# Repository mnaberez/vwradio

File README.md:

# VW Radios

This repository is all about reverse engineering older Volkswagen car radios, like the Premium 5 radio shown above.  The radios studied here are over fifteen years old and are the single-DIN size.  Despite their age, they are intelligent and support on-board diagnostics (using VW's KWP1281 protocol on the K-line).  You'll find notes about protocols and hardware here, along with partial disassembles of firmware, but no original binaries of firmware or EEPROMs.

VW radios from this era require a four digit security code often referred to as the "SAFE code". The radios usually store the SAFE code in a serial EEPROM like a 93C46 or a 24C04. The SAFE code can be found by opening up the radio, desoldering the EEPROM, reading it, and then soldering the EEPROM back in. I wanted to know if there was an easier way.

I disassembled the firmware for these radios: Premium 4 (Clarion), Premium 5 (Delco), Gamma 5 (TechniSat), and Rhapsody (TechniSat).  I found that all of them have backdoors to read the SAFE code via on-board diagnostics.  Reading the code this way means the radio does not need to be opened and may not even need to be removed from the car.  Since this information is not published anywhere and I couldn't find any tool that could do it, I built my own tool.

## Projects

- [`kwp1281_tool`](./kwp1281_tool/):  Diagnostics protocol tool (Volkswagen [KWP1281](https://translate.google.com/translate?hl=en&sl=de&tl=en&u=https%3A%2F%2Fde.wikipedia.org%2Fwiki%2FKWP1281)).  It can send arbitrary commands to a radio, or any other module, using the KWP1281 protocol.  It can also send commands using a proprietary protocol found in TechniSat radios.  Finally, it can automatically retrieve the SAFE code for any of the radios listed above.

- [`faceplate_emulator`](./faceplate_emulator/): Faceplate emulator (NEC [µPD16432B](http://6502.org/documents/datasheets/nec/nec_upd16432b_2000_dec.pdf)).  It plugs into the Premium 4 radio in place of the faceplate and allows the radio to be controlled over serial.  It can also simultaneously control a real faceplate.

- [`tape_emulator`](./tape_emulator/): Cassette tape emulator (Philips TDA3612).  It plugs into the Premium 4 radio in place of the SCA4.4/TDA3612 cassette tape assembly and fools the radio into thinking a tape is playing.

- [`volume_monitor`](./volume_monitor/): Volume monitor (Mitsubishi [M62419FP](https://web.archive.org/web/20180328173343/http://pdf.datasheetcatalog.com/datasheet/MitsubishiElectricCorporation/mXrwwyx.pdf)).
It connects in parallel with the M62419FP sound controller used in the Premium 4 radio and sends updates over serial whenever the sound registers are changed.

- [`reverse_engineering`](./reverse_engineering/): Notes about the radios from reverse engineering, including commented disassembly listings of radio firmware.  This repository does not contain any original firmware or EEPROM binaries.

## Discoveries

Here are some of the more interesting discoveries I made about the radios:

- All of the radios studied support a common set of KWP1281 diagnostics functions on the normal radio address of 0x56.  Some radios (not all) also have protected KWP1281 commands on this same address.  The protected commands available vary by model but may include the ability to read the microcontroller's ROM or RAM, and to read/write serial EEPROM(s).  Accessing the protected commands requires sending a login block based on the SAFE code and also performing a group reading of a hidden group.

- VW Premium 4 (Clarion) has an unprotected KWP1281 command 0xF0 that returns the SAFE code.  It also contains a hidden mode where the SAFE code can be changed via the faceplate.  Entering this mode requires pressing keys that do not exist on the faceplate.  I assume there was a special manufacturing faceplate used by the factory.

- VW Premium 5 (Delco) and Seat Liceo (Delco) respond to a different set of KWP1281 commands on address 0x7C.  These commands require authentication using a hardcoded login block.  Once authenticated, commands are available to read and write the EEPROM, which can be used to retrieve the SAFE code.

- VW Gamma 5 (TechniSat) and Rhapsody (TechniSat) have a proprietary, non-KWP protocol on address 0x7C.  It is unlike anything that I have found documented and was likely made by TechniSat just for manufacturing of the radio.  It has commands to read and write the EEPROM, which can be used to retrieve the SAFE code.  The SAFE code area of the EEPROM is normally filtered from these commands, but another command disables the filtering.

## Spin-offs

I also developed several other projects as a side effect of this work:

- [premium5](https://github.com/mnaberez/premium5): VW Premium 5 car radio emulator and debugger with a web-based interface

- [k0emu](https://github.com/mnaberez/k0emu): NEC 78K0 instruction set emulator with cycle counting and peripheral device support

- [k0dasm](https://github.com/mnaberez/k0dasm): NEC 78K0 disassembler that generates output compatible with the [as78k0](http://shop-pdp.net/ashtml/as78k0.htm) assember

- [f2mc8dump](https://github.com/mnaberez/f2mc8dump): Exploit to dump the internal ROM of Fujitsu F2MC-8L microcontrollers with external bus

- [f2mc8dasm](https://github.com/mnaberez/f2mc8dasm): Fujitsu F2MC-8 disassembler that generates output compatible with the [asf2mc8](http://shop-pdp.net/ashtml/asf2mc.htm) assembler

- [m740dasm](https://github.com/mnaberez/m740dasm): Mitsubishi 740 disassembler that generates output compatible with the [as740](http://shop-pdp.net/ashtml/as740.htm) assembler

## Author

[Mike Naberezny](https://github.com/mnaberez)

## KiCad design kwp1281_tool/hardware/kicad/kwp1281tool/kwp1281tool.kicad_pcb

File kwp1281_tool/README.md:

# KWP1281 Tool

## Overview

This is a USB interface that connects to the K-line of a vehicle's OBD port or to the K-line of a control module on a bench.  It uses a microcontroller that has been programmed to implement the [KWP1281](https://de.wikipedia.org/wiki/KWP1281) protocol.

When I reverse engineered the firmware for the VW Premium 4 radio, I found that it responds to several hidden KWP1281 commands.  I wanted to send these commands but I had no way to do so.  The commercial scan tool that I was using at the time did not provide any access to the underlying communications.  I built this project so I could directly interact with the Premium 4 radio using the raw KWP1281 protocol.  I have since used it successfully on other modules as well.

There are other open source projects that implement KWP1281 but this project is not based on any of them.  Therefore, it may have different features or problems than those other implementations.  VW did not release any documentation on KWP1281 to the public and I do not have any non-public information.  My implementation is based on my own [reverse engineering](../reverse_engineering/) of the diagnostics routines in several car radios, along with unofficial information posted by others online.

## Features

 - Galvanic isolation between the USB port and the OBD port
 - Automatically detects the baud rate of the module
 - Capable of sending and receiving raw KWP1281 blocks
 - Outputs a transcript of all KWP1281 blocks sent and received
 - Checks for errors whenever possible, during both transmit and receive
 - Reliably maintains a connection for long periods with modules tested

## Design

This project uses its own hardware based on a microcontroller.  It is not compatible with a "dumb" cable, "KKL" cable, or any commercial cable.  Please do not ask me to add support for any other cables.

When I started out on this project, I tried several "dumb" interfaces but found that communication was often unreliable due to timing problems, especially when transferring a lot of data or trying to communicate over long periods of time.  Here are some issues with "dumb" cables:

 - A module must be woken up with "slow init" by sending its address at a nonstandard baud rate (5 baud).  Since the computer must bit-bang the address byte when using a "dumb" cable, timing can be an issue.  The module may fail to recognize its address if any unexpected delays occur on the computer during bit-banging.

 - The protocol is designed for automatic baud rate detection.  After a module wakes up, it sends a sync byte (0x55) so that the receiver can measure its baud rate.  To detect the baud rate reliably, a timer with microsecond precision is needed.  This can't be done with a "dumb" cable so either the user has to pre-select a baud rate or various baud rates have to be blindly tried until one works.

 - Modules are sensitive to timing between bytes.  Once a connection is established, modules typically require a delay of one millisecond before each byte in a block is transmitted.  However, if the byte is delayed by too many milliseconds, the module may return "no acknowledge" or may abort the connection entirely.  Delays between the bytes caused by the computer's operating system multitasking or the USB to serial adapter can cause the KWP1281 connection to be unreliable when using a "dumb" cable.

This project uses a microcontroller to solve the above issues, which is how most commercial interfaces are implemented as well.  Again, please do not ask me to support other cables.

## Usage

Build the hardware as described in [`hardware/`](./hardware/).  Modify the [`main.c`](./firmware/main.c) file in the firmware for the KWP1281 communications you want to perform.  Build and flash the firmware.  Connect the board to the module.  When the board is powered up, it will begin KWP1281 communications immediately.  Use any terminal program to view the debug output.

Example code for `main.c`:
```
kwp_result_t result = kwp_connect(KWP_RADIO);
kwp_panic_if_error(result);

result = kwp_read_group(1);
kwp_panic_if_error(result);
```

Corresponding debug output:
```
CONNECT 56
BAUD: 10400 (DETECTED 10482)
KWRECV: 01 8A
KWSEND: 75
RECV: 0F AD F6 31 4A 30 30 33 35 31 38 30 42 20 20 03
PERFORM ACK
SEND: 03 AE 09 03
RECV: 0F AF F6 20 52 61 64 69 6F 20 44 45 32 20 20 03
PERFORM ACK
SEND: 03 B0 09 03
RECV: 0E B1 F6 20 20 20 20 20 20 20 30 30 30 31 03
PERFORM ACK
SEND: 03 B2 09 03
RECV: 08 B3 F6 00 03 21 86 9F 03
PERFORM ACK
SEND: 03 B4 09 03
RECV: 03 B5 09 03
VAG Number: "1J0035180B  "
Component:  " Radio DE2         0001"
PERFORM GROUP READ
SEND: 04 B6 29 01 03
RECV: 0F B7 E7 25 00 00 06 5F 80 17 64 00 25 00 87 03
MEAS: GROUP=01 CELL=01 FORMULA=25 VALUE=0000
MEAS: GROUP=01 CELL=02 FORMULA=06 VALUE=5F80
MEAS: GROUP=01 CELL=03 FORMULA=17 VALUE=6400
MEAS: GROUP=01 CELL=04 FORMULA=25 VALUE=0087
```

The tool has been tested successfully with over twenty different modules (mostly car radios).  It has been extensively tested with the the VW Premium 5 radio (Delco) and the VW Golf/Jetta Mk3 ABA 2.0L Motronic M5.9 ECU (Bosch).  It can maintain a connection reliably with these modules for hours.

## Pass-through Mode

Pass-through mode allows the host PC to directly control the K-line so that software written for "dumb" cables can be used with this interface.  Although I do not generally recommend this due to the issues with "dumb" cables noted above, the pass-through mode can be used if you need to run a piece of software that only supports "dumb" cables.

Enable the pass-through mode:

```
passthru_enable();
while(1);
```

In pass-through mode, the TXD and RXD of the onboard FT232RL are connected directly to the K-line via the L9637D.  The microcontroller's UARTs will still be able to receive data from the host PC and the K-line but they can't transmit to either.

Pass-through mode is also activated if the microcontroller is not installed or is held in reset.

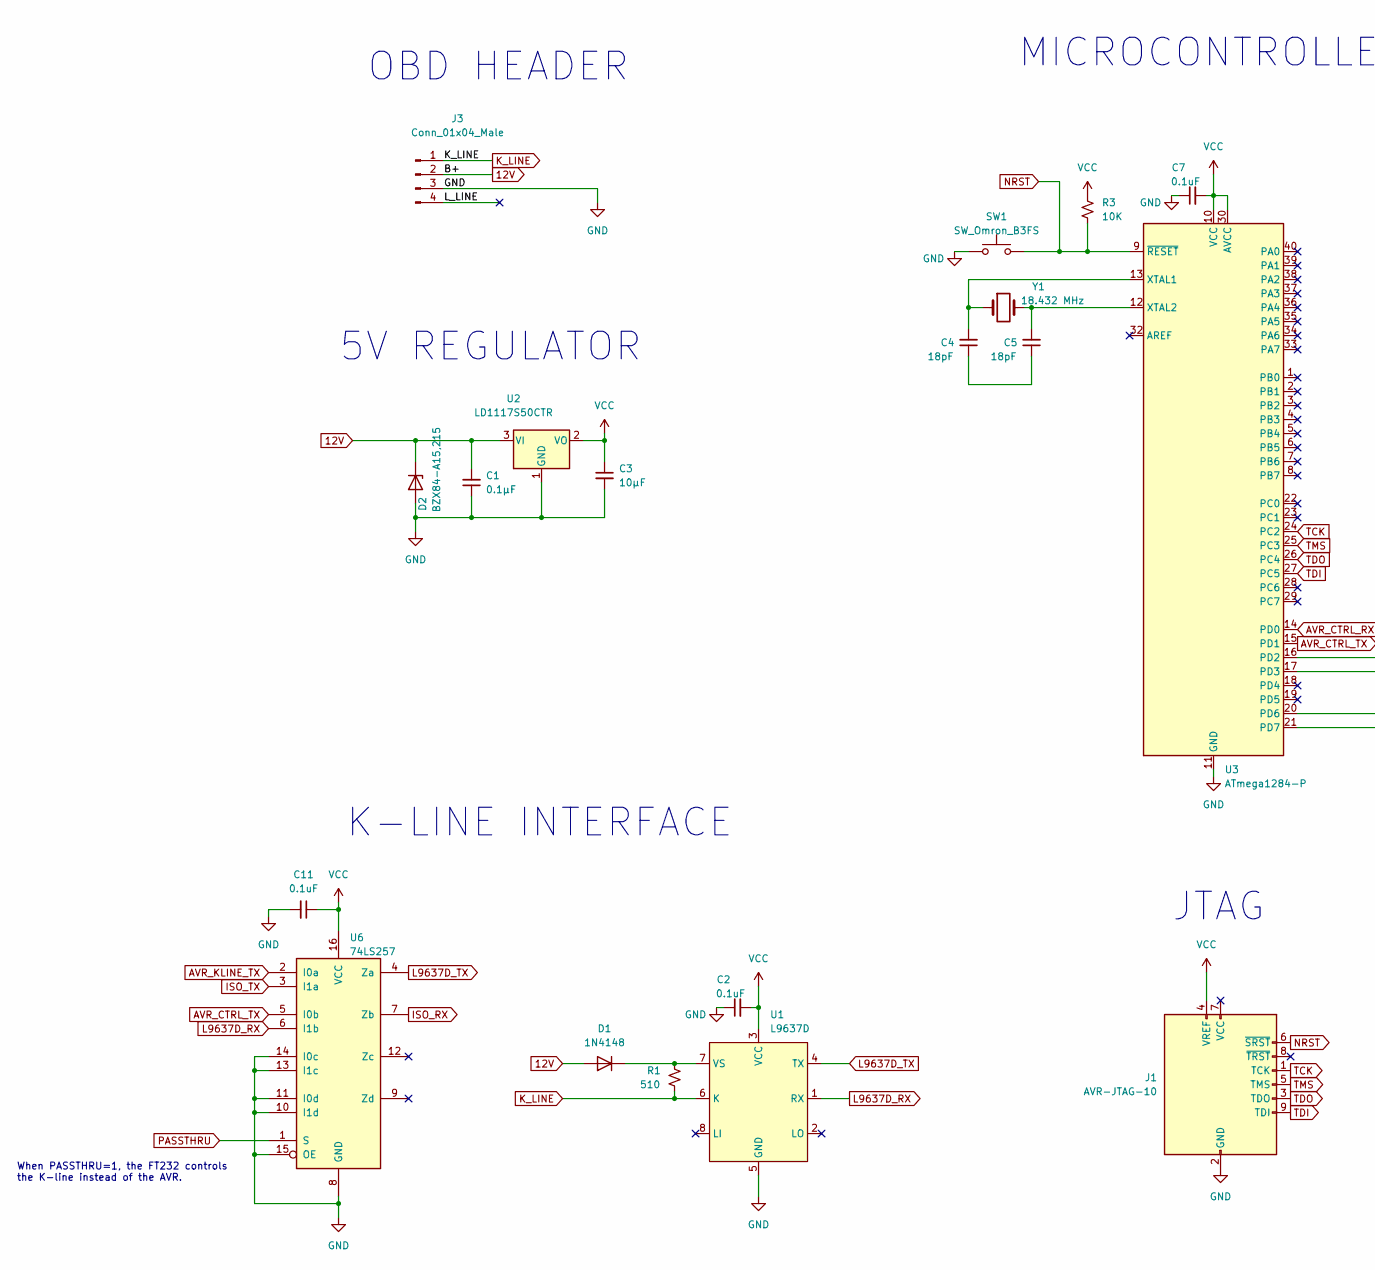
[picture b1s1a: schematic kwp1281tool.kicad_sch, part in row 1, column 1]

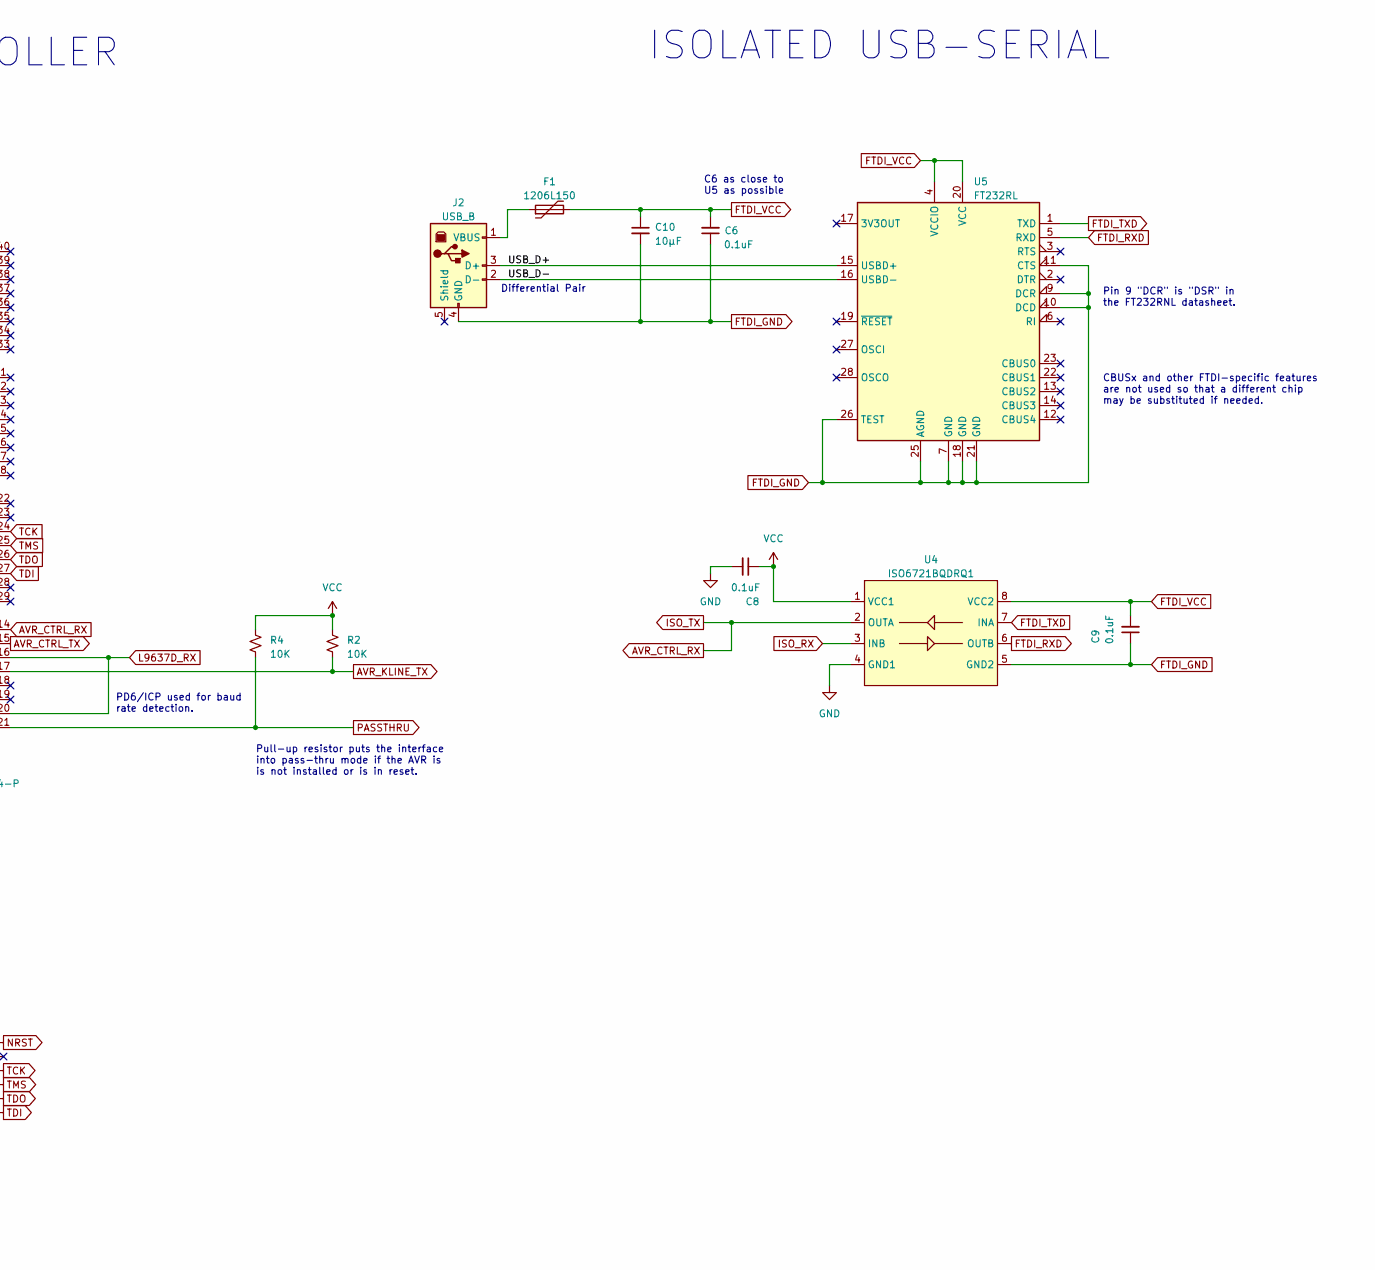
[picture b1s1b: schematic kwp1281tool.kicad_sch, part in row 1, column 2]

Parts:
C1: 0.1μF; C_0805_2012Metric_Pad1.18x1.45mm_HandSolder
C2, C6, C8, C9: 0.1uF; C_0805_2012Metric_Pad1.18x1.45mm_HandSolder
C3, C10: 10μF; C_0805_2012Metric_Pad1.18x1.45mm_HandSolder
C4, C5: 18pF; C_Disc_D5.0mm_W2.5mm_P5.00mm
C7, C11: 0.1uF; C_Disc_D5.0mm_W2.5mm_P5.00mm
D1: 1N4148; D_DO-35_SOD27_P7.62mm_Horizontal
D2: BZX84-A15,215; SOT-23
F1: 1206L150; Fuse_1206_3216Metric_Pad1.42x1.75mm_HandSolder
J1: AVR-JTAG-10; avr_jtag
J2: USB_B; USB_B_OST_USB-B1HSxx_Horizontal
J3: Conn_01x04_Male; PinHeader_1x04_P2.54mm_Horizontal
R1: 510; R_Axial_DIN0207_L6.3mm_D2.5mm_P15.24mm_Horizontal
R2, R3, R4: 10K; R_Axial_DIN0204_L3.6mm_D1.6mm_P7.62mm_Horizontal
SW1: SW_Omron_B3FS; SW_TH_Tactile_Omron_B3F-10xx
U1: L9637D; SOIC-8_3.9x4.9mm_P1.27mm
U2: LD1117S50CTR; SOT-223-3_TabPin2
U3: ATmega1284-P; DIP-40_W15.24mm
U4: ISO6721BQDRQ1; SOIC-8_3.9x4.9mm_P1.27mm
U5: FT232RL; SSOP-28_5.3x10.2mm_P0.65mm
U6: 74LS257; DIP-16_W7.62mm
Y1: 18.432 MHz; Crystal_HC49-4H_Vertical

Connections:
12V: C1.2, D1.2 (A), D2.3 (K), J3.2, U2.3 (VI)
/L_LINE: J3.4
/USB_D+: J2.3 (D+), U5.15 (USBD+)
/USB_D-: J2.2 (D-), U5.16 (USBD-)
AVR_CTRL_RX: U3.14 (PD0), U4.2 (OUTA), U6.3 (I1a)
AVR_CTRL_TX: U3.15 (PD1), U6.5 (I0b)
AVR_KLINE_TX: R2.2, U3.17 (PD3), U6.2 (I0a)
FTDI_GND: C6.1, C9.1, C10.2, J2.4 (GND), U4.5 (GND2), U5.7 (GND), U5.9 (DCR), U5.10 (DCD), U5.11 (CTS), U5.18 (GND), U5.21 (GND), U5.25 (AGND), U5.26 (TEST)
FTDI_RXD: U4.6 (OUTB), U5.5 (RXD)
FTDI_TXD: U4.7 (INA), U5.1 (TXD)
FTDI_VCC: C6.2, C9.2, C10.1, F1.2, U4.8 (VCC2), U5.4 (VCCIO), U5.20 (VCC)
GND: C1.1, C2.1, C3.2, C7.1, C8.2, C11.2, D2.1 (A), J1.2 (GND), J1.10 (GND), J3.3, SW1.1, U1.5 (GND), U2.1 (GND), U3.11 (GND), U3.31 (GND), U4.4 (GND1), U6.8 (GND), U6.10 (I1d), U6.11 (I0d), U6.13 (I1c), U6.14 (I0c), U6.15 (OE)
ISO_RX: U4.3 (INB), U6.7 (Zb)
K_LINE: J3.1, R1.2, U1.6 (K)
L9637D_RX: U1.1 (RX), U3.16 (PD2), U3.20 (PD6), U6.6 (I1b)
L9637D_TX: U1.4 (TX), U6.4 (Za)
NRST: J1.6 (~SRST), R3.2, SW1.2, U3.9 (~RESET)
unnamed: C4.1, C5.1
unnamed: D1.1 (K), R1.1, U1.7 (VS)
unnamed: F1.1, J2.1 (VBUS)
unnamed: C4.2, U3.13 (XTAL1), Y1.1
unnamed: C5.2, U3.12 (XTAL2), Y1.2
PASSTHRU: R4.2, U3.21 (PD7), U6.1 (S)
TCK: J1.1 (TCK), U3.24 (PC2)
TDI: J1.9 (TDI), U3.27 (PC5)
TDO: J1.3 (TDO), U3.26 (PC4)
TMS: J1.5 (TMS), U3.25 (PC3)
VCC: C2.2, C3.1, C7.2, C8.1, C11.1, J1.4 (VREF), R2.1, R3.1, R4.1, U1.3 (VCC), U2.2 (VO), U3.10 (VCC), U3.30 (AVCC), U4.1 (VCC1), U6.16 (VCC)

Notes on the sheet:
When PASSTHRU=1, the FT232 controls the K-line instead of the AVR.
PD6/ICP used for baud rate detection.
MICROCONTROLLER
K-LINE INTERFACE
CBUSx and other FTDI-specific features are not used so that a different chip may be substituted if needed.
5V REGULATOR
Pull-up resistor puts the interface into pass-thru mode if the AVR is is not installed or is in reset.
Pin 9 "DCR" is "DSR" in the FT232RNL datasheet.
C6 as close to U5 as possible
OBD HEADER
ISOLATED USB-SERIAL
Differential Pair
JTAG

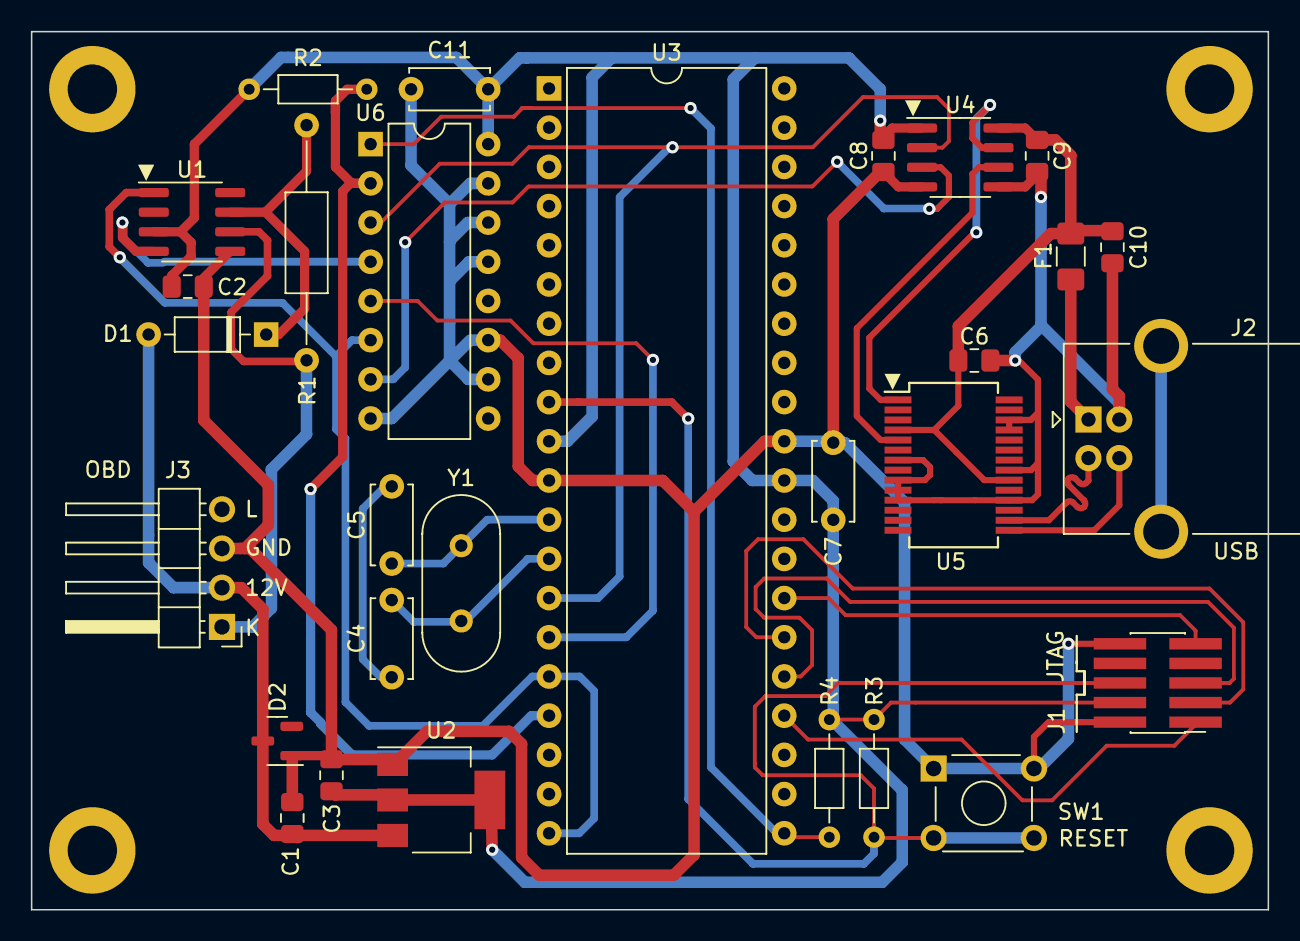
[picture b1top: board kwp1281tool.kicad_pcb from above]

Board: 2 copper layers, 80.1 x 56.9 mm, 29 parts (0 on the bottom side), 27 nets.

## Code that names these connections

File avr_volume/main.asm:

;VW Premium IV Radio (Clarion PU-1666A) Volume Monitor
;
;Passively captures SPI commands from the radio's microcontroller to its
;Mitsubishi M62419FP sound controller, decodes the commands, computes
;the programmed attenuator values in dB, then dumps the values out
;the UART at 115200 bps, N-8-1.
;
;Atmel ATMega1284 running at 20 MHz
;
;Pin  9: /RESET to GND through pushbutton, 10K pullup to Vcc
;               also connect to Atmel-ICE AVR port pin 6 nSRST
;Pin 10: Vcc (connect to radio's 5V)
;Pin 11: GND (connect to radio's GND)
;Pin 12: XTAL2 (to 20 MHz crystal with 18pF cap to GND)
;Pin 13: XTAL1 (to 20 MHz crystal and 18pF cap to GND)
;...
;Pin 15: PD1/TXD (to PC's serial RXD)
;...
;Pin 24: PC2 JTAG TCK (to Atmel-ICE AVR port pin 1 TCK)
;Pin 25: PC3 JTAG TMS (to Atmel-ICE AVR port pin 5 TMS)
;Pin 26: PC4 JTAG TDO (to Atmel-ICE AVR port pin 3 TDO)
;Pin 27: PC5 JTAG TDI (to Atmel-ICE AVR port pin 9 TDI)
;...
;Pin 30: AVCC connect directly to Vcc (also to Atmel-ICE AVR port pin 4 VTG)
;Pin 31: GND (also to Atmel-ICE AVR port pins 2 GND and 10 GND)
;Pin 32: AREF connect to GND through 0.1 uF cap
;...
;Pin 39: PA1 M62419FP Clock
;Pin 40: PA0 M62419FP Data
;

.include "m1284def.asm"


.equ ram             = SRAM_START
;Buffers for M62419FP command packets (isr buf -> rx buf -> work buf)
.equ packet_bitcount = ram      ;Counts down bits remaining to rx in packet
.equ packet_isr_buf  = ram+$01  ;2 bytes to accumulate SPI packet bits in ISR
.equ packet_rx_buf   = ram+$03  ;2 bytes for complete SPI packet received
.equ packet_work_buf = ram+$05 	;2 bytes for SPI packet used during parsing
;Buffer used to track M62419FP state across commands
.equ m62419fp_buf    = ram+$07  ;12 byte buffer for M62419FP state


;Offsets into M62419FP state buffer
.equ ch0             = 0                ;Channel 0 (Right):
.equ ch0_att1        = ch0+0            ;  ATT1 5-bit code
.equ ch0_att2        = ch0+1            ;  ATT2 2-bit code
.equ ch0_loudness    = ch0+2            ;  Loudness flag (0=off, 1=on)
.equ ch0_input       = ch0+3            ;  Input selector 2-bit code
.equ ch1             = ch0_input+1      ;Channel 1 (Left):
.equ ch1_att1        = ch1+0            ;  ATT1 5-bit code
.equ ch2_att2        = ch1+1            ;  ATT2 2-bit code
.equ ch3_loudness    = ch1+2            ;  Loudness bit (0=off, 1=on)
.equ ch4_input       = ch1+3            ;  Input selector 2-bit code
.equ common          = ch4_input+1      ;Common to both channels:
.equ fadesel         = common+0         ;  Fader Select flag (0=front, 1=rear)
.equ fader           = common+1         ;  Fader 4-bit code
.equ bass            = common+2         ;  Bass 4-bit tone code
.equ treble          = common+3         ;  Treble 4-bit tone code


.org 0
    rjmp reset

.org PCI0addr
	rjmp spi_isr_pcint0

.org 0+INT_VECTORS_SIZE


reset:
	ldi r16, low(RAMEND) 		;Initialize the stack pointer
	out SPL, r16
	ldi r16, high(RAMEND)
	out SPH, r16

	rcall uart_init 			;15200 bps, N-8-1
	rcall spi_init              ;Set up for M62419FP receive on interrupt
	sei                         ;Enable interrupts

loop:
    ;Set Y-pointer to a buffer that will receive a packet
    ldi YL, low(packet_work_buf)
    ldi YH, high(packet_work_buf)

    ;Set Z-pointer to M62419FP registers buffer
    ldi ZL, low(m62419fp_buf)
    ldi ZH, high(m62419fp_buf)

wait:
    ;Wait for an M62419FP command packet
    rcall spi_get_packet        ;Try to get a new packet into bufer at Y
    brcc wait                   ;Loop until one is ready

    rcall cmd_parse             ;Parse command at Y into registers at Z
    rcall cmd_parse             ;Parse command at Y into registers at Z
    rcall dump_to_uart
    rjmp loop


dump_to_uart:
;Dump the virtual M62419FP register state to the UART, along with
;the calculated attenuation values in dB.
;
;Format of the dump:
;  Byte  0: Number of bytes to follow
;  Byte  1: CH0 ATT1 5-bit code
;  Byte  2: CH0 ATT2 2-bit code
;  Byte  3: CH0 Attenuation (ATT1+ATT2) in signed dB
;  Byte  4: CH0 Loudness flag
;  Byte  5: CH0 Input Selector 2-bit code
;  Byte  6: CH1 ATT1 5-bit code
;  Byte  7: CH1 ATT2 2-bit code
;  Byte  8: CH1 Attenuation (ATT1+ATT2) in signed dB
;  Byte  9: CH1 Loudness flag
;  Byte 10: CH1 Input Selector 2-bit code
;  Byte 11: Fader Select flag
;  Byte 12: Fader 4-bit code
;  Byte 13: Fader Attenuation in signed dB
;  Byte 14: Bass 4-bit code
;  Byte 15: Bass tone in signed dB
;  Byte 16: Treble 4-bit code
;  Byte 17: Treble tone in signed dB
;
;Destroys R16, R17, R18, Z-pointer.
;
    ldi r16, 17
    rcall uart_send_byte        ;Send number of bytes to follow
    clr r18                     ;Channel number = 0
dump_loop:
    ;Set Z-pointer to buffer area for channel 0 or 1
    ldi ZL, low(m62419fp_buf)   ;Base address of M62419FP registers buffer
    ldi ZH, high(m62419fp_buf)
    sbrc r18, 0                 ;Skip next instruction if this is channel 0
    adiw ZH:ZL, ch1             ;Add offset for channel 1 registers

    ;Send ATT1 and ATT2 codes, calculate ATT1+ATT2 in dB and send it
    ld r16, Z+                  ;Load ATT1 code
    rcall uart_send_byte        ;Send it
    rcall cmd_calc_att1_db      ;Convert ATT1 to signed dB
    push r16                    ;Save ATT1 dB on the stack
    ld r16, Z+                  ;Load ATT2 code
    rcall uart_send_byte        ;Send it
    rcall cmd_calc_att2_db      ;Convert it to signed dB
    mov r17, r16                ;Move ATT2 dB into R17
    pop r16                     ;Recall ATT1 dB into R16
    rcall cmd_calc_att_sum_db   ;Caculate sum of R16 + R17 in signed dB
    rcall uart_send_byte        ;Send it

    ;Send other registers
    ld r16, Z+                  ;Load and send loudness
    rcall uart_send_byte
    ld r16, Z+                  ;Load and send input selector
    rcall uart_send_byte

    inc r18                     ;Increment channel number
    cpi r18, 2                  ;Finished both channels?
    brne dump_loop              ;  No: dump next channel

    ;Set Z-pointer to buffer area for fader
    ldi ZL, low(m62419fp_buf+common)
    ldi ZH, high(m62419fp_buf+common)

    ld r16, Z+                  ;Load and send fader select
    rcall uart_send_byte

    ld r16, Z+                  ;Load fader 4-bit code
    rcall uart_send_byte        ;Send it
    rcall cmd_calc_fader_db     ;Convert it to signed dB
    rcall uart_send_byte        ;Send it

    ld r16, Z+                  ;Load bass 4-bit code
    rcall uart_send_byte        ;Send it
    rcall cmd_calc_tone_db      ;Convert it to signed dB
    rcall uart_send_byte        ;Send it

    ld r16, Z+                  ;Load treble 4-bit code
    rcall uart_send_byte        ;Send it
    rcall cmd_calc_tone_db      ;Convert it to signed dB
    rcall uart_send_byte        ;Send it
    ret


.include "m62419fp_spi.asm"     ;M62419FP SPI receive
.include "m62419fp_cmd.asm"     ;M52419FP SPI command packet parsing
.include "uart.asm"             ;UART routines

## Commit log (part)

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2019-08-07 Found more sub_0c48 tables
2019-08-09 Found more code locations
2019-08-09 Remove hardcoded addresses
2019-08-09 Found block length in memory
2019-08-09 Comment unknown KWP1281 code
2019-08-10 Progress on KWP1281 initialization
2019-08-13 Add comments with text for states
2019-08-13 Fix pointers to group reading tables
2019-08-13 Add comments for I/O used in bit-banging address
2019-08-18 Progress on address 0x3f security access
2019-08-18 Found bit that controls SAFE mode lock/unlock
2019-08-22 Allow configuration of F_CPU via Makefile
2019-08-23 Add support for 8 and 16 MHz crystals
2019-08-23 Remove unused functions
2019-08-23 Fix "if" that should be "else if"
2019-09-06 Clarify error code description
2019-09-07 Add KWP1281 addresses to filenames
2019-09-08 Fix printing VAG number with "extra info" bit set
2019-09-09 Confirmed address 0x3f is the instrument cluster
2019-10-31 Use #pragma once
2019-10-31 Fix functions with no parameters
2019-10-31 Fix missing #pragma once
2019-11-02 Remove _autobaud_ prefix from statics
2019-11-09 Fix uninitialized variable warning
    kwp1281.c: In function ‘kwp_connect’:
    kwp1281.c:870:8: warning: ‘keyword’ may be used uninitialized in this function [-Wmaybe-uninitialized]
    if (keyword != KWP_1281) { return KWP_BAD_KEYWORD; }
    ^
2019-11-29 Fix power-on glitch on UART TX line
2019-11-29 Add serial loopback firmware
2019-11-29 Rename loopback/ to loopback_poll/
2019-11-29 Rename "forever" to "irq_unexpected"
2019-11-29 Add comments to UART0 error handling
2019-11-29 Implement serial loopback on interrupt
2019-11-29 Handle UART0 receive errors
2019-11-30 Add unmodified "SOFTWARE 23" firmware as a base for loopback
2019-11-30 Loopback works while radio firmware is running
2019-11-30 Fix description of transmit buffer
2019-11-30 Add notes on LED output latch
2019-12-01 Found the STOP/EJECT key
2019-12-03 Remove obsolete test program
2019-12-03 Comment more uPD16432B SPI routines
2019-12-04 Found key data buffer direct from uPD16432B
2019-12-04 Progress on key scan code
2019-12-04 Improve disassembly of LED latch and custom chars
2019-12-05 Found the alarm LED
2019-12-05 Found RAM clear routines, comment more I/O
2019-12-07 Add comments to interrupt register changes
2019-12-08 Found binary to BCD conversion
2019-12-08 Found check for valid EEPROM or memory address
2019-12-08 Annotate CALLT instructions
2019-12-08 Found table of bytes lookup at sub_0c7d
2019-12-09 Use .rept to build the filler areas
2019-12-10 Improve description of sub_0b0d
2019-12-10 Add comments to KWP1281 group reading
2019-12-13 Found the bottom of the stack
2019-12-13 Comment unknown EEPROM routine
2019-12-14 Start flashing instructions
2019-12-14 Fix hardcoded values in tables
2019-12-14 Add Python 3.8 to Travis config
2019-12-14 Add more comments to KWP1281 read RAM/EEPROM checks
2019-12-20 Comment more subroutines
2019-12-20 Found SAFE code digit updates
2019-12-21 Comment ROM checksum routine
2019-12-21 Found nibble to ASCII digit conversion
2019-12-21 Found an insane number of copies of sub_6809
2019-12-23 Found multiplication routine at sub_0b9c
2019-12-24 Found subtraction routine at sub_09ef
2019-12-26 Found table of nibbles lookup at sub_0c64
2019-12-27 Comment FIS routines
2019-12-30 Found more hardcoded FIS lengths
2019-12-31 Found I2C addresses
2019-12-31 Progress on I2C routines
2020-01-01 Fix code at lab_795b
2020-01-01 Fix jump table at mem_cf7d
2020-01-02 Fix description of sub_306f
2020-01-03 Add flash instructions
2020-01-11 Remove support for 8 MHz crystal
2020-01-11 Fix part number and description of Delco 16181209
2020-01-12 Found MFSW connection
2020-01-12 Confirmed CSI31 is CD Changer (CDC)
2020-01-15 Found uPD16432B /LCDOFF control
2020-01-16 Fix INTP6 label
2020-01-22 Update copyright year to 2020
2020-01-25 Rename interrupt handlers for known functions
2020-01-26 Fix position in table
2020-01-26 Found cassette tape METAL sensor
2020-02-01 Remove obsolete test firmware
2020-02-02 Start mapping out unknown I/O
2020-02-03 Found Monsoon amplifier power control
2020-02-10 Found analog input routines
2020-02-17 Found illumination analog input
2020-02-20 Progress on fault codes
2020-02-21 Clarify process of receiving faults
2020-02-21 Add usage for sub_274e
2020-02-23 Progress on reading measuring blocks
2020-02-23 Add comments to security result processing
2020-02-27 Found output test sequencer
2020-03-05 Add comments to identification blocks
2020-03-05 Found routine that validates coding
2020-03-05 Found subroutine that changes the coding
2020-03-05 Recoding also changes workshop code
2020-03-06 Found subroutines to get coding and workshop code
2020-03-14 Improve description of coding request/response
2020-03-15 Fix indentation
2020-03-16 Add info on connection blocks
2020-03-23 Comment KWP1281 disconnect and session state
2020-03-24 Rename "end session" to "disconnect"
2020-03-24 Send disconnect block and wait to disconnect
2020-03-25 Explain NAK responses
2020-03-26 Receive buffer is significantly larger than previously thought
2020-03-27 Mark uses of kwp_addresses table index
2020-03-27 Found RX buffer overflow check
2020-03-27 Found tx buffer index and byte used for error detection
2020-03-28 Give better names to many KWP1281 locations
2020-03-29 Build on xenial, add ARM toolchain
2020-03-29 Improve description of parsing address and length
2020-03-30 Found CD changer buffers
2020-03-30 Found CDC TX pin
2020-04-04 Found SAFE code sanitization during EEPROM read
2020-04-12 Found EEPROM write after successful login
2020-04-13 Found unknown login bit that influences coding
2020-04-13 Add notes on login side effects
2020-04-14 Handle 0xE7 string response
2020-04-22 Add note that 40 bytes is the size of the VAG 1552's LCD
2020-06-04 Implement write RAM command
2020-06-04 Found write RAM command (0x45)
2020-06-05 Clean up and document Rhapsody firmware dump RCE
2020-06-09 Add initial disassembly of Seat Liceo radio
2020-06-27 Clarify that K-line "mode" is the resistor
2020-07-02 Revert accidental change to main
2020-07-02 Add note that TechniSat fixed the KWP1281 block counter bug
2020-07-02 Add photos of VW Rhapsody
2020-07-02 Add photos of VW Premium 5
2020-07-02 Add photos of VW Gamma 5 (TechniSat)
2020-07-03 Add photos of VW SAM 2002 (Delco)
2020-07-04 Automatically crack VW SAM 2002 radio
2020-07-04 Add EEPROM notes for SAM 2002
2020-07-21 Add notes on firmware versions
2020-07-30 Fix error code not being surfaced by tsat_rce_read_memory()
2020-07-31 Found delay routine
2020-07-31 Found more code areas
2020-07-31 Fix disassembly of TechniSat command 0x53
2020-07-31 Disable EEPROM filter does not work on Skoda Symphony
2020-07-31 Remove debugging leftover
2020-07-31 Start work on Skoda Symphony
2020-08-01 Automatically crack Skoda Symphony
2020-08-07 Add whitespace for readability
2020-08-18 Fix broken link
2020-08-22 Command 0x58 sets unknown location 0x342
2020-08-22 Use better labels for KWP1281 functions
2020-08-22 Mark probable I2C functions
2020-08-22 SAFE code retrieval works on Skoda Symphony MP3 SKZA7H
2020-08-24 Progress on TechniSat protocol I2C commands
2020-08-25 Finish disassembly of command 0x42 response
2020-08-28 Found routine that writes coding to EEPROM
2020-08-29 Further progress on SAFE code EEPROM routines
2020-08-30 Add missing labels
2020-09-08 Add missing label for mem_36d5
2021-01-03 Add GitHub Actions workflow
2021-04-10 Add constants for watchdog settings
2021-04-12 Use a constant for BRGC0 value
2021-04-12 Disable builds failing due to missing PPA
2021-04-14 Add a test firmware that continously transmits out the UART
2021-04-14 Add LED blink to serial test firmware
2021-04-18 Found unused RAM areas
2021-04-26 Build using new asxxxx 5.40 with as78k0 patches
2021-05-07 Progress on measuring blocks, S-Contact, EEPROM
2021-05-08 Found more KWP1281 locations
2021-05-08 Add notes on title 0xD7 request to cluster
2021-06-16 Add ability to receive 5 baud address
2021-10-28 Automatically crack VW Konzern 2004 MP3 radio
2021-10-28 Add script to extract memory dump from log
2021-10-28 Add SHA1 for Konzern 2004 MP3 firmware
2021-10-28 Add function to dump firmware from Delco radios
2021-11-10 Automatically crack VW Konzern 2004 DAC radio
2021-12-07 Detect another VW Konzern 2004 MP3 part number
2022-01-11 Install asxxxx from GitHub
2022-01-12 Build using ASxxxx 5.40 Update 4 (2021-12-16)
2022-01-30 Found code that descrambles 0x3D block from cluster
2022-01-30 Found KWP1281 routines for unlock from cluster
2022-01-30 Found more cluster KWP1281 code
2022-01-30 Found Cluster ID in EEPROM
2022-02-02 Found cluster unlock routines
2022-02-02 Found many EEPROM locations in RAM
2022-02-02 Found Cluster ID in Liceo RAM
2022-02-03 Found 0xD7 request block
2022-02-03 Use label to indicate return only
2022-02-03 Read Cluster ID from TechniSat Gamma 5
2022-02-05 Found AM/FM frequency location
2022-02-05 Found station presets
2022-02-06 Found region setting in EEPROM
2022-02-06 Found more region code, fix hardcoded addresses at mem_adae
2022-02-06 Found EEPROM area in RAM clear routine
2022-02-07 Found 4 extra BASS/MID/TREB areas in EEPROM
2022-02-07 Found initialization of EEPROM defaults
2022-02-07 Use better names for common subroutines
2022-02-08 Use better names for EEPROM routines
2022-02-08 Found MFSW button codes
2022-02-10 Found MFSW buffer and timer
2022-02-10 Found unused copies of MFSW tables
2022-02-13 Found more CDC TX routines
2022-02-13 Found most CDC commands
2022-02-14 Found CD track time (minutes, seconds)
2022-02-14 Found CD number
2022-02-14 Add labels for more messages
2022-02-15 Found temporarily-displayed messages
2022-02-16 Found Terminal 30 measurement
2022-02-17 Found group of analog inputs
2022-02-18 Add constants for unique measurement ids
2022-02-18 Found S-Contact on/off values
2022-02-20 Comment I/O changes related to the K-line
2022-02-21 Progress on startup code
2022-02-26 Protected areas contain Coding and Workshop Code
2022-02-26 Improve disassembly of unlock-from-cluster routines
2022-03-12 Add instructions for flashing with HEF40106BT still installed
2022-03-12 Move MFSW info to premium_5/
2022-03-13 Convert many UART calls to printf()
2022-04-30 Add another SAM 2002 part number
2022-07-11 Port volume monitor project to ASAVR assembler
2022-07-11 Update docs now that AVRA fork is no longer required
2022-10-29 Upgrade GitHub Actions steps to fix deprecation warnings
2022-12-11 Run utilities on Python 3 by default
2022-12-15 Mark unused strings
2023-04-21 E7 3F does not work on all VAG-1552 cards
2023-06-15 Use 18.432 MHz crystal for less UART error
2023-06-21 Add more info on timing issues
2023-06-25 Update copyright year to 2023
2023-06-25 Ignore KiCad preferences and backups
2023-06-25 Add KWP1281 tool schematic as PDF
2023-06-25 Add directory for Gerber outputs
2023-07-01 Integrate USB onto the board
2023-07-01 Add KWP1281 tool rev 2 gerbers sent to production
2023-07-01 Remove outdated TODO list
2023-07-01 Add new photo of rev 1 board
2023-07-07 Add KWP1281 tool rev 3 gerbers sent to production
2023-07-07 Add KWP1281 tool rev 3 schematic as PDF
2023-07-12 Add new photo of rev 2 board
2023-07-13 Add new photo of rev 3 board
2023-07-13 Disable pass-thru mode on startup
2023-07-13 Add pass-through mode to README
2024-08-07 Found EEPROM mirrors in RAM and checksum routines
2024-08-19 Found more I2C routines
2024-08-21 Found mfg commands to read or write ranges of exposed addresses
2024-08-22 Found all regions available for arbitrary read/write
2024-08-27 Found flags for I2C start and stop conditions
2024-08-27 Document all options for I2C read/write command
2024-08-28 Add script to find addresses available for arbitrary read/write
2024-09-01 Add comments to I2C calls
2024-09-02 Found antenna phantom power (Fernspeisung) control
2024-09-18 Upgrade to KiCad 8
2025-02-27 Handle 0x02/0xF4 group reading response
2025-03-14 Fix missing space in error message
2025-03-15 Add address for 1J0909603 airbag controller
2025-03-15 Add support for clearing faults on 037906023AC
2026-04-24 Improve MFSW disassembly
2026-04-25 Found a third EEPROM checksum
2026-04-25 Run tests on more Python versions
2026-04-25 Add MFSW notes
2026-05-18 Fix swapped MFSW button codes

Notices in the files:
kwp1281_tool/hardware/kicad/kwp1281tool/kwp1281tool.kicad_pcb:
© 2023 MIKE NABEREZNY
